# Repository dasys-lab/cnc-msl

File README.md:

# cnc-msl 
[Reference](https://carpe-noctem-cassel.github.io/cnc-msl) | [Documentation](https://carpe-noctem-cassel.github.io)

Domain-specific stuff of Carpe Noctem Cassel Middle Size League stuff...

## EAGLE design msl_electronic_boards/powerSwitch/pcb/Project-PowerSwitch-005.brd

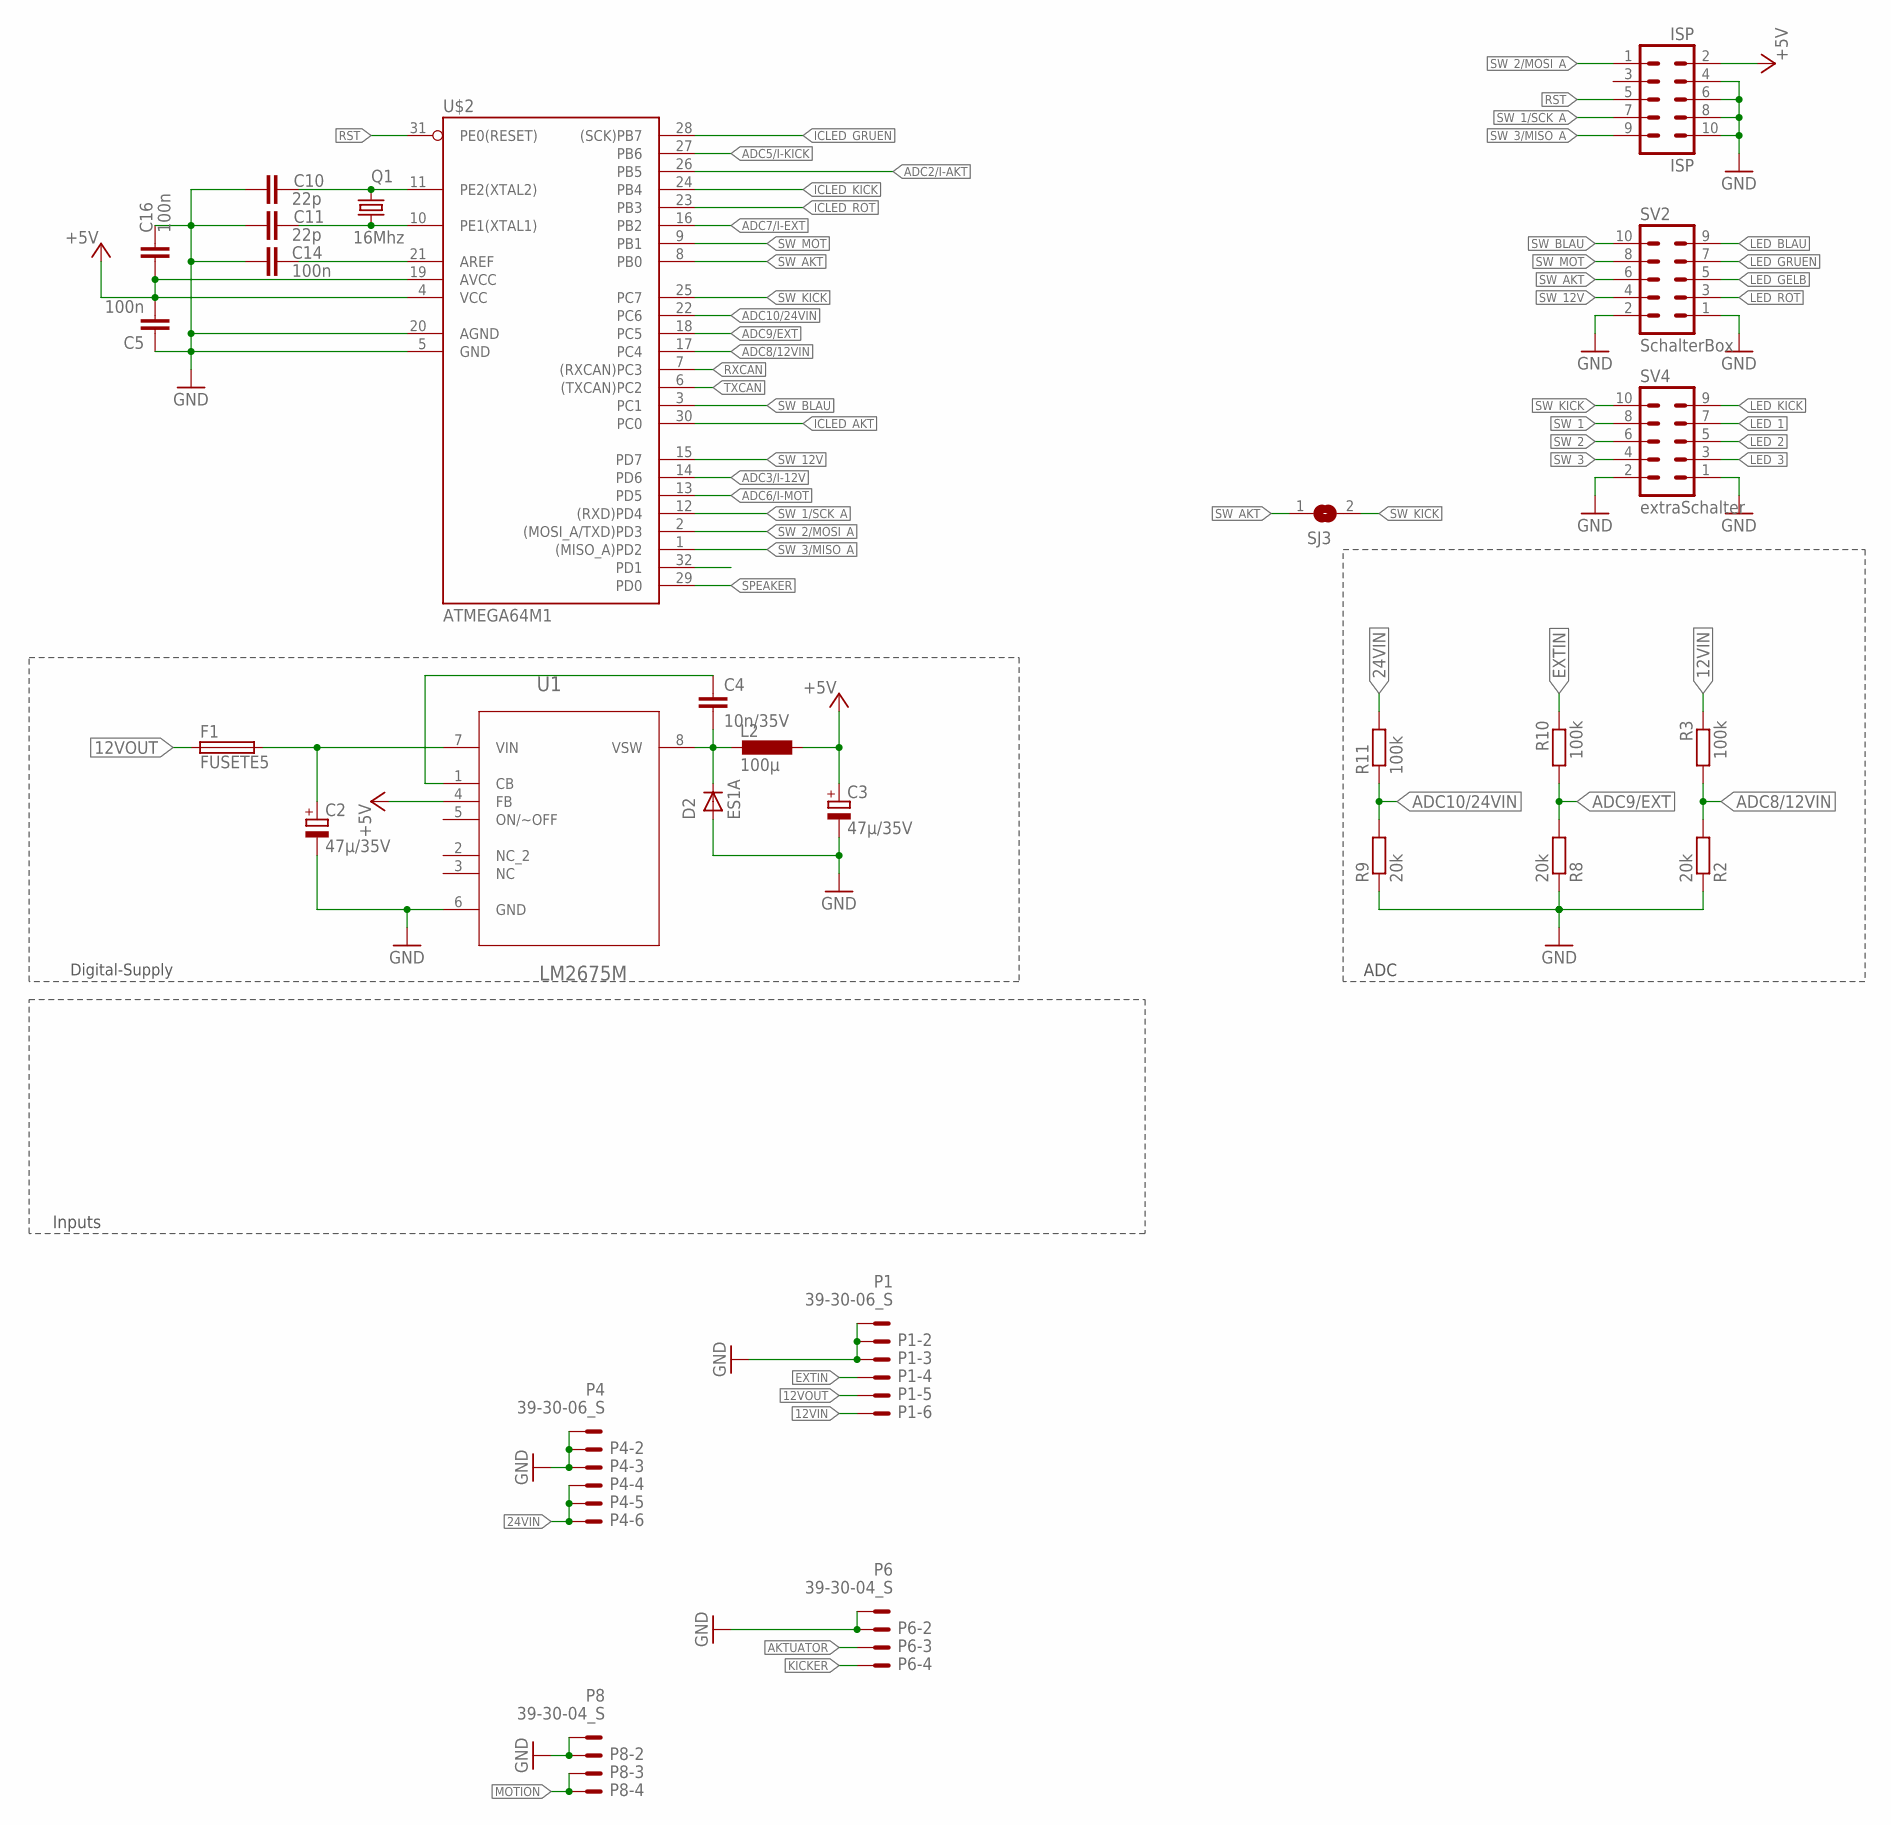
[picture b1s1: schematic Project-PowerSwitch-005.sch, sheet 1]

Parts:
C2, C3: 47µ/35V; PANASONIC_D
C4: 10n/35V; C0603
C5, C14, C16: 100n; C0603
C10, C11: 22p; C0603
D2: ES1A; SMA-DO214AC
F1: FUSETE5; TE5
ISP: ISP; ML10
L2: 100µ; PISM
P1, P4: 39-30-06_S; 39-30-?06?
P6, P8: 39-30-04_S; 39-30-?04?
Q1: 16Mhz; HC49UP
R2, R8, R9: 20k; R0805
R3, R10, R11: 100k; R0805
SJ3: SJ
SV2: SchalterBox; ML10
SV4: extraSchalter; ML10
U1: LM2675M; SOIC127P620X175-8N
U$2: ATMEGA64M1; TQFP32-08

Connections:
12VIN: P1.6, R3.1; also elsewhere on the board
12VOUT: F1.1, P1.5; also elsewhere on the board
24VIN: P4.4, P4.5, P4.6, R11.2; also elsewhere on the board
+5V: C3.+, C5.2, C16.1, ISP.2, L2.1, U1.4 (FB), U$2.4 (VCC), U$2.19 (AVCC); also elsewhere on the board
ADC2/I-AKT: U$2.26 (PB5); also elsewhere on the board
ADC3/I-12V: U$2.14 (PD6); also elsewhere on the board
ADC5/I-KICK: U$2.27 (PB6); also elsewhere on the board
ADC6/I-MOT: U$2.13 (PD5); also elsewhere on the board
ADC7/I-EXT: U$2.16 (PB2); also elsewhere on the board
ADC8/12VIN: R2.2, R3.2, U$2.17 (PC4)
ADC9/EXT: R8.2, R10.2, U$2.18 (PC5)
ADC10/24VIN: R9.2, R11.1, U$2.22 (PC6)
AKTUATOR: P6.3; also elsewhere on the board
EXTIN: P1.4, R10.1; also elsewhere on the board
GND: C2.-, C3.-, C5.1, C10.1, C11.1, C14.1, C16.2, D2.A, ISP.4, ISP.6, ISP.8, ISP.10, P1.1, P1.2, P1.3, P4.1, P4.2, P4.3, P6.1, P6.2, P8.1, P8.2, R2.1, R8.1, R9.1, SV2.1, SV2.2, SV4.1, SV4.2, U1.6 (GND), U$2.5 (GND), U$2.20 (AGND); also elsewhere on the board
ICLED_AKT: U$2.30 (PC0); also elsewhere on the board
ICLED_GRUEN: U$2.28 ((SCK)PB7); also elsewhere on the board
ICLED_KICK: U$2.24 (PB4); also elsewhere on the board
ICLED_ROT: U$2.23 (PB3); also elsewhere on the board
KICKER: P6.4; also elsewhere on the board
LED_1: SV4.7
LED_2: SV4.5
LED_3: SV4.3
LED_BLAU: SV2.9; also elsewhere on the board
LED_GELB: SV2.5; also elsewhere on the board
LED_GRUEN: SV2.7; also elsewhere on the board
LED_KICK: SV4.9; also elsewhere on the board
LED_ROT: SV2.3; also elsewhere on the board
MOTION: P8.3, P8.4; also elsewhere on the board
unnamed: C10.2, Q1.2, U$2.11 (PE2(XTAL2))
unnamed: C11.2, Q1.1, U$2.10 (PE1(XTAL1))
unnamed: C14.2, U$2.21 (AREF)
unnamed: C2.+, F1.2, U1.7 (VIN)
unnamed: C4.2, D2.K (C), L2.2, U1.8 (VSW)
unnamed: C4.1, U1.1 (CB)
RST: ISP.5, U$2.31 (PE0(RESET))
RXCAN: U$2.7 ((RXCAN)PC3); also elsewhere on the board
SPEAKER: U$2.29 (PD0); also elsewhere on the board
SW_1: SV4.8
SW_1/SCK_A: ISP.7, U$2.12 ((RXD)PD4)
SW_2: SV4.6
SW_2/MOSI_A: ISP.1, U$2.2 ((MOSI_A/TXD)PD3)
SW_3: SV4.4
SW_3/MISO_A: ISP.9, U$2.1 ((MISO_A)PD2)
SW_12V: SV2.4, U$2.15 (PD7); also elsewhere on the board
SW_AKT: SJ3.1, SV2.6, U$2.8 (PB0); also elsewhere on the board
SW_BLAU: SV2.10, U$2.3 (PC1)
SW_KICK: SJ3.2, SV4.10, U$2.25 (PC7); also elsewhere on the board
SW_MOT: SV2.8, U$2.9 (PB1); also elsewhere on the board
TXCAN: U$2.6 ((TXCAN)PC2); also elsewhere on the board

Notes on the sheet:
Inputs
ADC
Digital-Supply

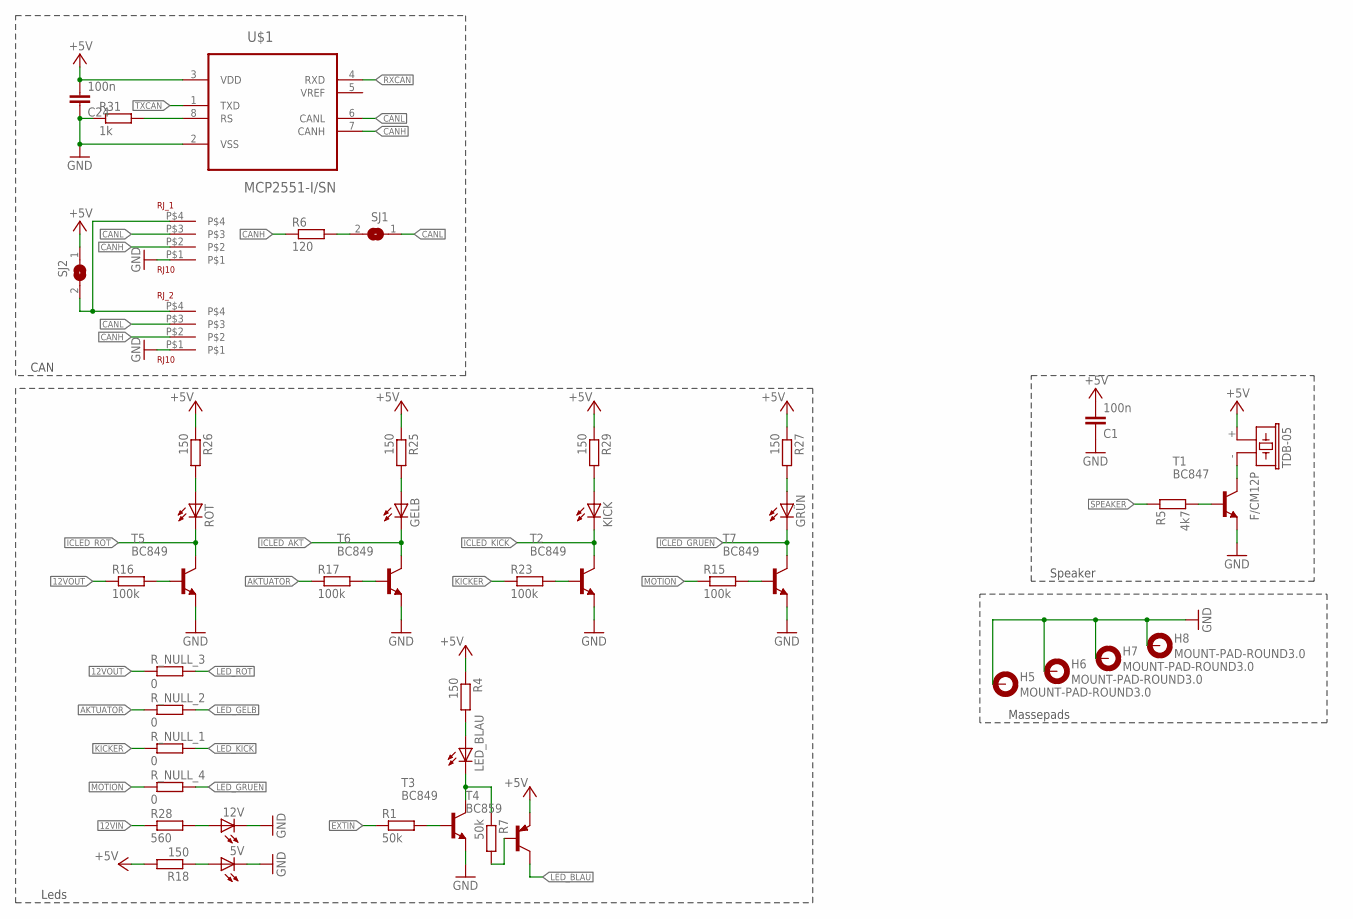
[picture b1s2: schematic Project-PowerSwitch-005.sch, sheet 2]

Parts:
5V, 12V: LEDCHIPLED_0805; CHIPLED_0805
C1, C24: 100n; C0603
GELB: LEDCHIPLED_0805; CHIPLED_0805
GRÜN: LEDCHIPLED_0805; CHIPLED_0805
H5, H6, H7, H8: MOUNT-PAD-ROUND3.0; 3,0-PAD
KICK: LEDCHIPLED_0805; CHIPLED_0805
LED_BLAU: LEDCHIPLED_0805; CHIPLED_0805
R1, R7: 50k; R0805
R4, R18, R25, R26, R27, R29: 150; R0805
R5: 4k7; R0805
R6: 120; M0805
R15, R16, R17, R23: 100k; R0805
R28: 560; R0805
R31: 1k; R0805
RJ_1, RJ_2: RJ10
ROT: LEDCHIPLED_0805; CHIPLED_0805
R_NULL_1, R_NULL_2, R_NULL_3, R_NULL_4: 0; R0402
SJ1, SJ2: SJ
T1: BC847; SOT23
T2, T3, T5, T6, T7: BC849; SOT23
T4: BC859; SOT23-BEC
TDB-05: F/CM12P
U$1: MCP2551-I/SN; SOIC127P600X175-8N

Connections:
12VIN: R28.1; also elsewhere on the board
12VOUT: R16.1, R_NULL_3.1; also elsewhere on the board
+5V: C1.2, C24.2, R4.1, R18.2, R25.1, R26.1, R27.1, R29.1, SJ2.1, T4.E, TDB-05.+ (1), U$1.3 (VDD); also elsewhere on the board
AKTUATOR: R17.1, R_NULL_2.1; also elsewhere on the board
CANH: R6.1, RJ_1.P$2, RJ_2.P$2, U$1.7 (CANH)
CANL: RJ_1.P$3, RJ_2.P$3, SJ1.1, U$1.6 (CANL)
EXTIN: R1.1; also elsewhere on the board
GND: 5V.C, 12V.C, C1.1, C24.1, H5.B3,0, H6.B3,0, H7.B3,0, H8.B3,0, R31.1, RJ_1.P$1, RJ_2.P$1, T1.2 (E), T2.2 (E), T3.2 (E), T5.2 (E), T6.2 (E), T7.2 (E), U$1.2 (VSS); also elsewhere on the board
ICLED_AKT: GELB.C, T6.3 (C); also elsewhere on the board
ICLED_GRUEN: GRÜN.C, T7.3 (C); also elsewhere on the board
ICLED_KICK: KICK.C, T2.3 (C); also elsewhere on the board
ICLED_ROT: ROT.C, T5.3 (C); also elsewhere on the board
KICKER: R23.1, R_NULL_1.1; also elsewhere on the board
LED_BLAU: T4.C; also elsewhere on the board
LED_GELB: R_NULL_2.2; also elsewhere on the board
LED_GRUEN: R_NULL_4.2; also elsewhere on the board
LED_KICK: R_NULL_1.2; also elsewhere on the board
LED_ROT: R_NULL_3.2; also elsewhere on the board
MOTION: R15.1, R_NULL_4.1; also elsewhere on the board
unnamed: R5.2, T1.1 (B)
unnamed: RJ_1.P$4, RJ_2.P$4, SJ2.2
unnamed: R23.2, T2.1 (B)
unnamed: KICK.A, R29.2
unnamed: R31.2, U$1.8 (RS)
unnamed: R6.2, SJ1.2
unnamed: GELB.A, R25.2
unnamed: R26.2, ROT.A
unnamed: R1.2, T3.1 (B)
unnamed: LED_BLAU.A, R4.2
unnamed: LED_BLAU.C, R7.1, T3.3 (C)
unnamed: R7.2, T4.B
unnamed: T1.3 (C), TDB-05.- (2)
unnamed: GRÜN.A, R27.2
unnamed: 12V.A, R28.2
unnamed: R16.2, T5.1 (B)
unnamed: R17.2, T6.1 (B)
unnamed: R15.2, T7.1 (B)
unnamed: 5V.A, R18.1
RXCAN: U$1.4 (RXD); also elsewhere on the board
SPEAKER: R5.1; also elsewhere on the board
TXCAN: U$1.1 (TXD); also elsewhere on the board

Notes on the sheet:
CAN
Speaker
Massepads
Leds

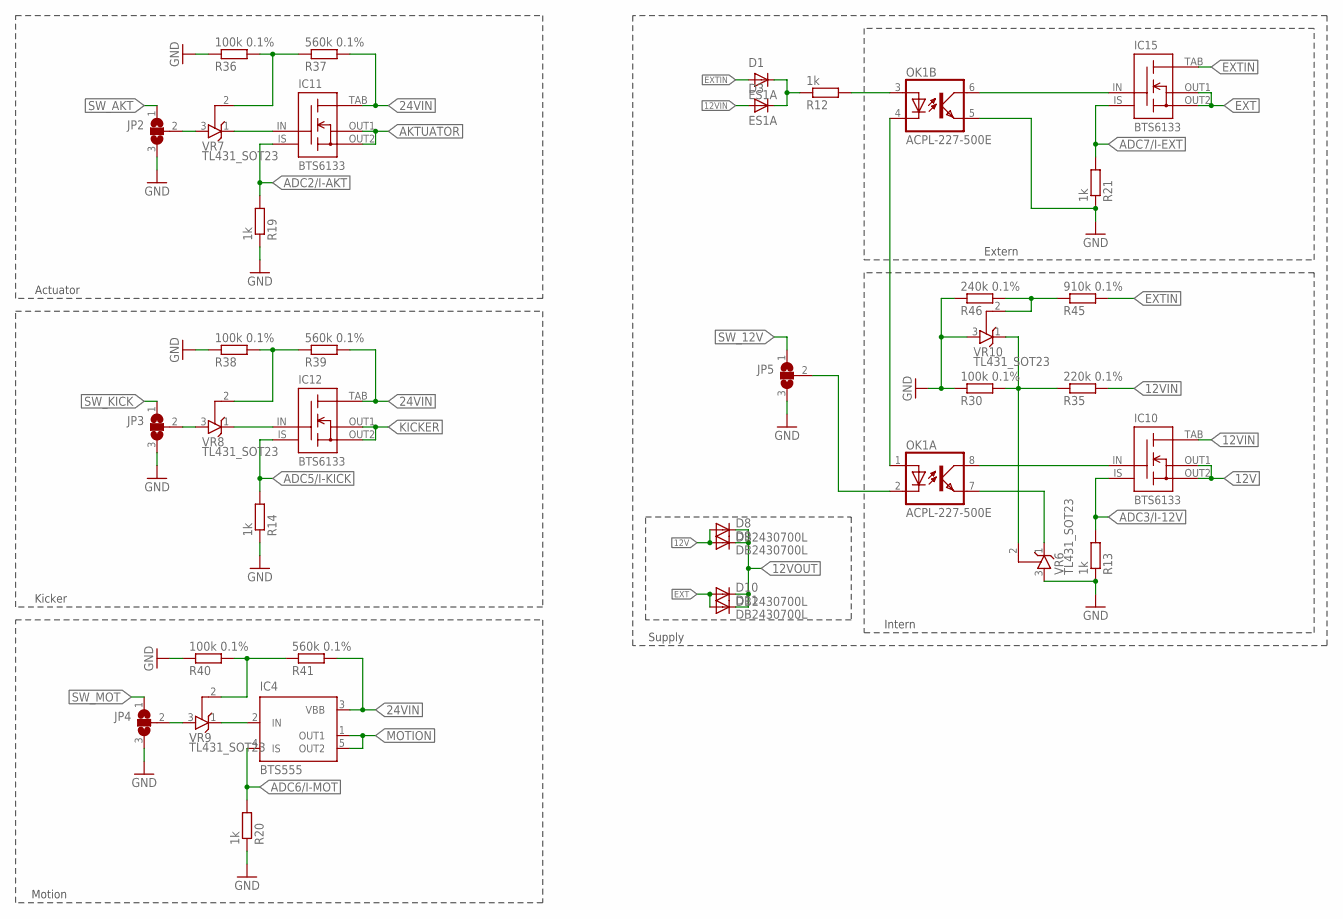
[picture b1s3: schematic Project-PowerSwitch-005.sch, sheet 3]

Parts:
D1, D3: ES1A; SMA-DO214AC
D8, D9, D10, D11: DB2430700L; TMINIP2-F2-B
IC4: BTS555; TO220-51
IC10, IC11, IC12, IC15: BTS6133; TO252-51
JP2, JP3, JP4, JP5: SJ2W; SJ_2
OK1: ACPL-227-500E; SOIC08
R12, R13, R14, R19, R20, R21: 1k; R0805
R30, R36, R38, R40: 100k 0.1%; R0805
R35: 220k 0.1%; R0805
R37, R39, R41: 560k 0.1%; R0805
R45: 910k 0.1%; R0805
R46: 240k 0.1%; R0805
VR6, VR7, VR8, VR9, VR10: TL431_SOT23; SOT23

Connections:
12V: D8.A, D9.A, IC10.OUT1 (OUT), IC10.OUT2 (OUT)
12VIN: D3.A, IC10.TAB (VBB), R35.2; also elsewhere on the board
12VOUT: D8.C, D9.C, D10.C, D11.C; also elsewhere on the board
24VIN: IC4.3 (VBB), IC11.TAB (VBB), IC12.TAB (VBB), R37.2, R39.2, R41.2; also elsewhere on the board
ADC2/I-AKT: IC11.IS, R19.2; also elsewhere on the board
ADC3/I-12V: IC10.IS, R13.2; also elsewhere on the board
ADC5/I-KICK: IC12.IS, R14.2; also elsewhere on the board
ADC6/I-MOT: IC4.4 (IS), R20.2; also elsewhere on the board
ADC7/I-EXT: IC15.IS, R21.2; also elsewhere on the board
AKTUATOR: IC11.OUT1 (OUT), IC11.OUT2 (OUT); also elsewhere on the board
EXT: D10.A, D11.A, IC15.OUT1 (OUT), IC15.OUT2 (OUT)
EXTIN: D1.A, IC15.TAB (VBB), R45.2; also elsewhere on the board
GND: JP2.3, JP3.3, JP4.3, JP5.3, OK1.5 (EMIT), R13.1, R14.1, R19.1, R20.1, R21.1, R30.1, R36.1, R38.1, R40.1, R46.1, VR6.3 (A), VR10.3 (A); also elsewhere on the board
KICKER: IC12.OUT1 (OUT), IC12.OUT2 (OUT); also elsewhere on the board
MOTION: IC4.1 (OUT1), IC4.5 (OUT2); also elsewhere on the board
unnamed: JP2.2, VR7.3 (A)
unnamed: JP5.2, OK1.2 (C)
unnamed: JP3.2, VR8.3 (A)
unnamed: JP4.2, VR9.3 (A)
unnamed: D1.K (C), D3.K (C), R12.1
unnamed: OK1.1 (A), OK1.4 (C)
unnamed: OK1.3 (A), R12.2
unnamed: OK1.7 (EMIT), VR6.1 (C)
unnamed: IC15.IN, OK1.6 (COL)
unnamed: IC10.IN, OK1.8 (COL)
unnamed: R30.2, R35.1, VR6.2 (R), VR10.1 (C)
unnamed: IC12.IN, VR8.1 (C)
unnamed: IC4.2 (IN), VR9.1 (C)
unnamed: IC11.IN, VR7.1 (C)
unnamed: R36.2, R37.1, VR7.2 (R)
unnamed: R38.2, R39.1, VR8.2 (R)
unnamed: R40.2, R41.1, VR9.2 (R)
unnamed: R45.1, R46.2, VR10.2 (R)
SW_12V: JP5.1; also elsewhere on the board
SW_AKT: JP2.1; also elsewhere on the board
SW_KICK: JP3.1; also elsewhere on the board
SW_MOT: JP4.1; also elsewhere on the board

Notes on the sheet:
Intern
Extern
Supply
Motion
Kicker
Actuator

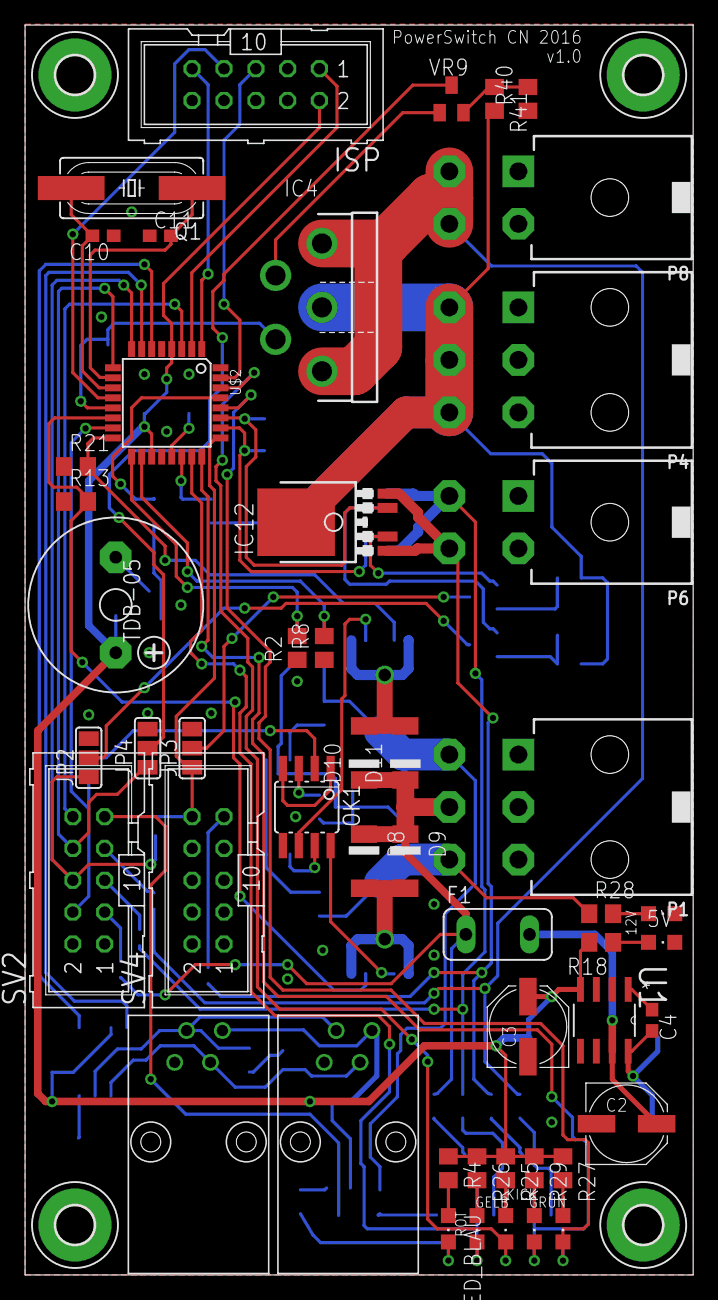
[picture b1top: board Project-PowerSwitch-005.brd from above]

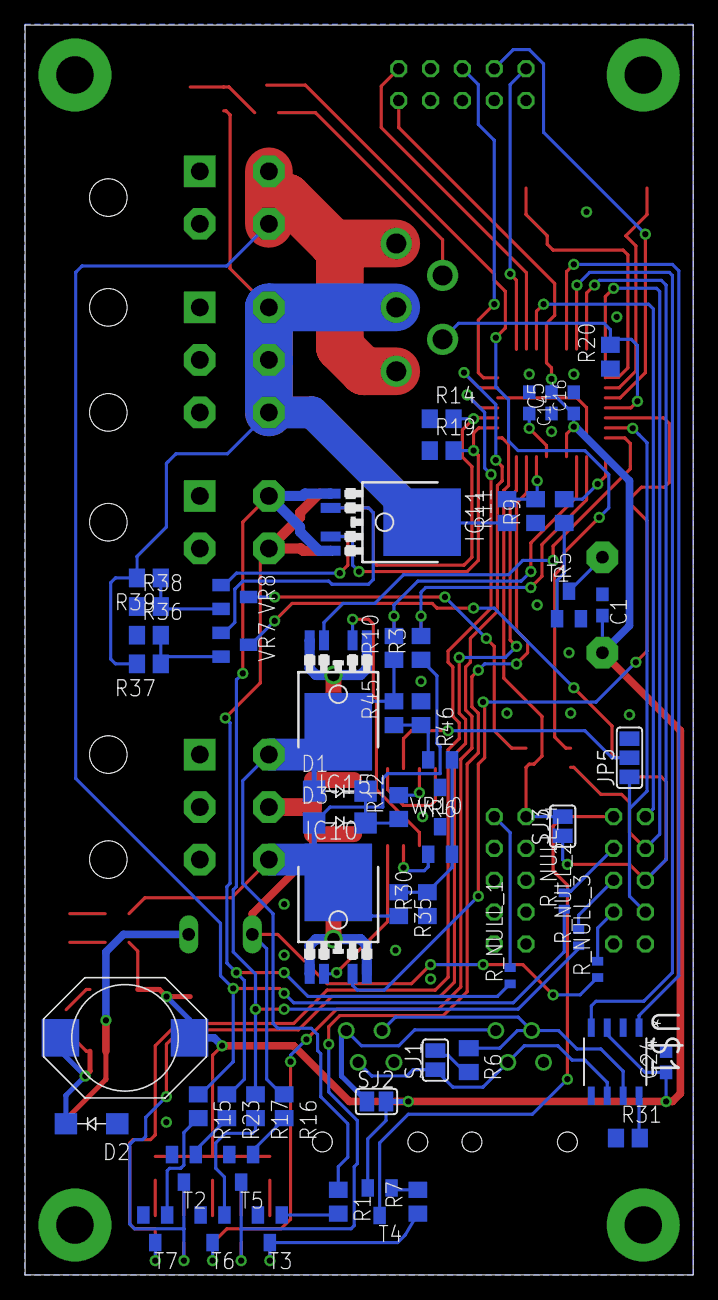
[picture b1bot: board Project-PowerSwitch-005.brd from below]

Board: 4 copper layers, 53.3 x 99.7 mm, 111 parts (57 on the bottom side), 85 nets.

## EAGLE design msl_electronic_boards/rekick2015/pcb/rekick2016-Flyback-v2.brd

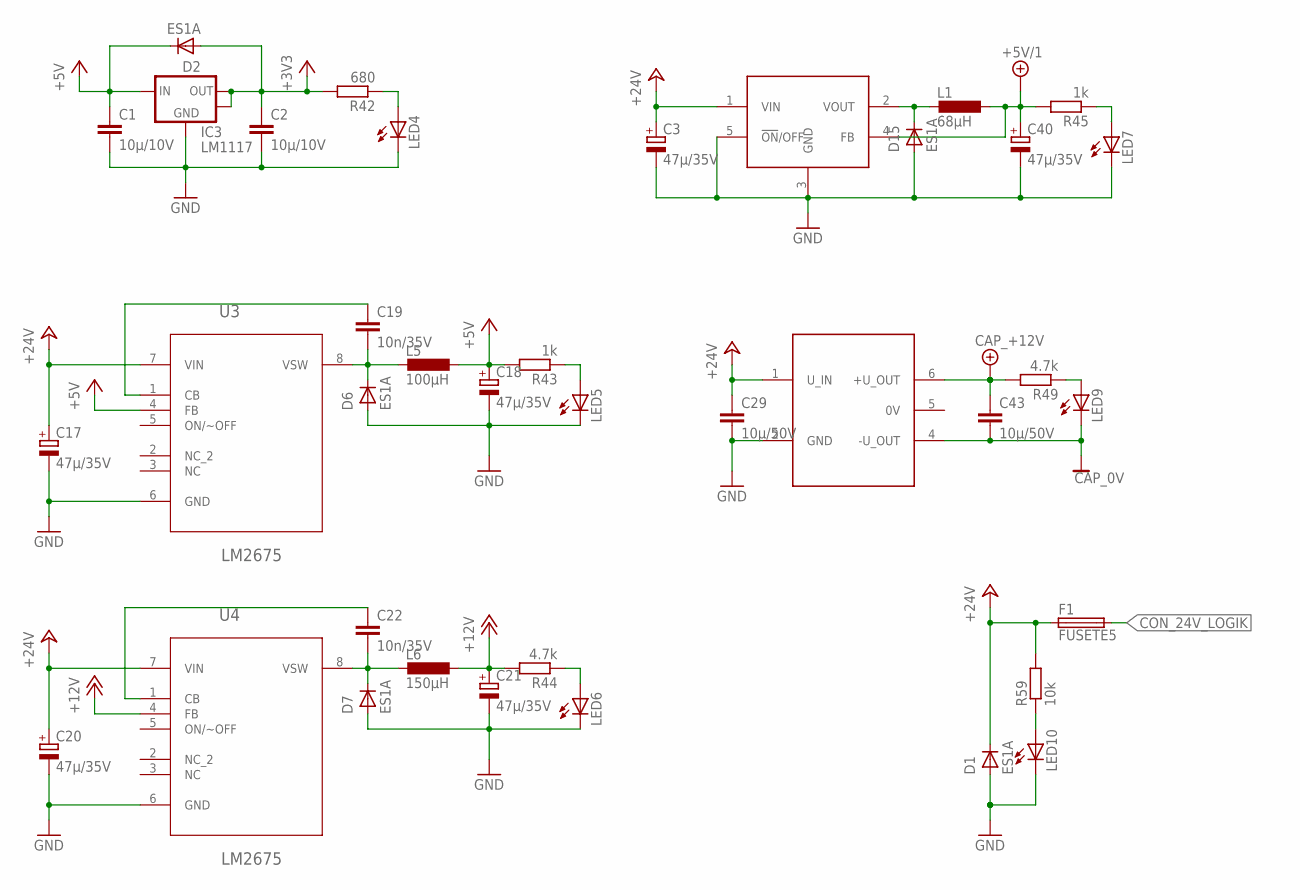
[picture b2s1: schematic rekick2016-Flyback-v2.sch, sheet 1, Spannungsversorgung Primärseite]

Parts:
C1, C2: 10µ/10V; C0603
C3, C17, C18, C20, C21, C40: 47µ/35V; PANASONIC_D
C19, C22: 10n/35V; C0603
C29, C43: 10µ/50V; C1206
D1, D2, D6, D7, D15: ES1A; SMA-DO214AC
F1: FUSETE5; TE5
IC3: LM1117; SOT223
L1: 68µH; PISM
L5: 100µH; PISM
L6: 150µH; PISM
LED4, LED5, LED6, LED7, LED9, LED10: LEDCHIP-LED0805; CHIP-LED0805
R42: 680; R0805
R43, R45: 1k; R0805
R44, R49: 4.7k; R0805
R59: 10k; R0805
U3, U4: LM2675; SOIC127P620X175-8N
U$4: TMH-D
U$8: LM2576; TO220511

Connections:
+3V3: C2.1, D2.A, IC3.2 (OUT), IC3.4 (OUT), R42.2; also elsewhere on the board
+5V: C1.1, C18.+, D2.K (C), IC3.3 (IN), L5.1, R43.2, U3.4 (FB); also elsewhere on the board
+5V/1: C40.+, L1.1, R45.2, U$8.4 (FB); also elsewhere on the board
+12V: C21.+, L6.1, R44.2, U4.4 (FB); also elsewhere on the board
+24V: C3.+, C17.+, C20.+, C29.1, D1.K (C), F1.1, R59.2, U3.7 (VIN), U4.7 (VIN), U$4.1 (U_IN), U$8.1 (VIN); also elsewhere on the board
CAP_0V: C43.2, LED9.C, U$4.4 (-U_OUT); also elsewhere on the board
CAP_+12V: C43.1, R49.2, U$4.6 (+U_OUT); also elsewhere on the board
CON_24V_LOGIK: F1.2; also elsewhere on the board
GND: C1.2, C2.2, C3.-, C17.-, C18.-, C20.-, C21.-, C29.2, C40.-, D1.A, D6.A, D7.A, D15.A, IC3.1 (GND), LED4.C, LED5.C, LED6.C, LED7.C, LED10.C, U3.6 (GND), U4.6 (GND), U$4.2 (GND), U$8.3 (GND), U$8.5 (!ON!/OFF); also elsewhere on the board
unnamed: C19.2, D6.K (C), L5.2, U3.8 (VSW)
unnamed: C19.1, U3.1 (CB)
unnamed: C22.2, D7.K (C), L6.2, U4.8 (VSW)
unnamed: C22.1, U4.1 (CB)
unnamed: LED4.A, R42.1
unnamed: D15.K (C), L1.2, U$8.2 (VOUT)
unnamed: LED7.A, R45.1
unnamed: LED5.A, R43.1
unnamed: LED6.A, R44.1
unnamed: LED9.A, R49.1
unnamed: LED10.A, R59.1

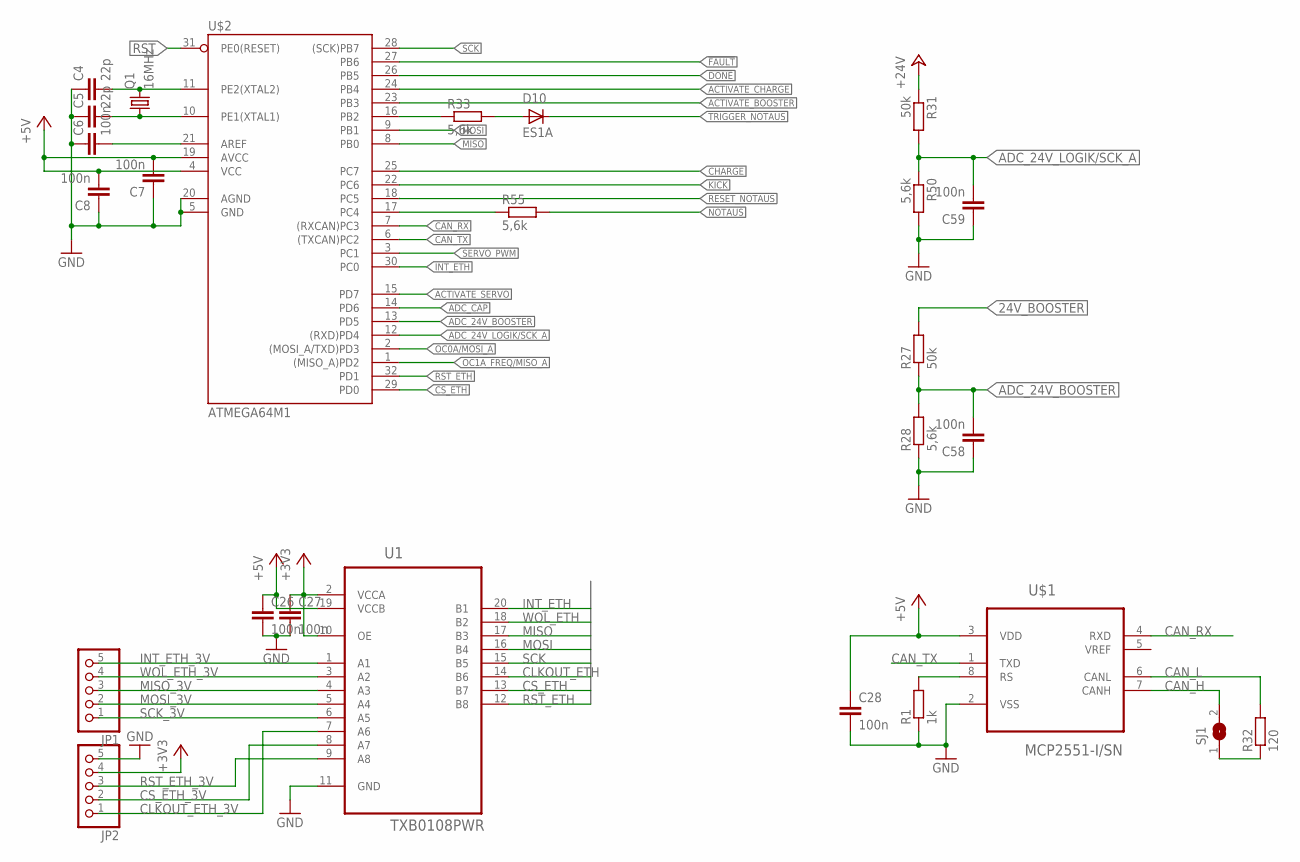
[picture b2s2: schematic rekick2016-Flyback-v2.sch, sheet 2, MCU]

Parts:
C4, C5: 22p; C0603
C6, C7, C8, C26, C27, C28, C58, C59: 100n; C0603
D10: ES1A; SMA-DO214AC
JP1, JP2: PINHD-1X5; 1X05
Q1: 16MHz; HC49UP
R1: 1k; R0805
R27, R31: 50k; R0805
R28, R33, R50, R55: 5,6k; R0805
R32: 120; R0805
SJ1: SJ
U1: TXB0108PWR; SOP65P640X120-20N
U$1: MCP2551-I/SN; SOIC127P600X175-8N
U$2: ATMEGA64M1; TQFP32-08

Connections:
24V_BOOSTER: R27.2; also elsewhere on the board
!DONE: U$2.26 (PB5); also elsewhere on the board
!FAULT: U$2.27 (PB6); also elsewhere on the board
+3V3: C27.1, JP2.4, U1.2 (VCCA), U1.10 (OE); also elsewhere on the board
+5V: C7.2, C8.2, C26.1, C28.1, U1.19 (VCCB), U$1.3 (VDD), U$2.4 (VCC), U$2.19 (AVCC); also elsewhere on the board
+24V: R31.1; also elsewhere on the board
ACTIVATE_BOOSTER: U$2.23 (PB3); also elsewhere on the board
ACTIVATE_CHARGE: U$2.24 (PB4); also elsewhere on the board
ACTIVATE_SERVO: U$2.15 (PD7); also elsewhere on the board
ADC_24V_BOOSTER: C58.2, R27.1, R28.2, U$2.13 (PD5)
ADC_24V_LOGIK/SCK_A: C59.2, R31.2, R50.1, U$2.12 ((RXD)PD4); also elsewhere on the board
ADC_CAP: U$2.14 (PD6); also elsewhere on the board
CAN_H: SJ1.2, U$1.7 (CANH); also elsewhere on the board
CAN_L: R32.2, U$1.6 (CANL); also elsewhere on the board
CAN_RX: U$1.4 (RXD), U$2.7 ((RXCAN)PC3)
CAN_TX: U$1.1 (TXD), U$2.6 ((TXCAN)PC2)
CHARGE: U$2.25 (PC7); also elsewhere on the board
CLKOUT_ETH: U1.14 (B6)
CLKOUT_ETH_3V: JP2.1, U1.7 (A6)
CS_ETH: U1.13 (B7), U$2.29 (PD0)
CS_ETH_3V: JP2.2, U1.8 (A7)
GND: C4.1, C5.1, C6.1, C7.1, C8.1, C26.2, C27.2, C28.2, C58.1, C59.1, JP2.5, R1.1, R28.1, R50.2, U1.11 (GND), U$1.2 (VSS), U$2.5 (GND), U$2.20 (AGND); also elsewhere on the board
INT_ETH: U1.20 (B1), U$2.30 (PC0)
INT_ETH_3V: JP1.5, U1.1 (A1)
IN_NOTAUS: R55.1, U$2.17 (PC4)
KICK: U$2.22 (PC6); also elsewhere on the board
MISO: U1.17 (B3), U$2.8 (PB0)
MISO_3V: JP1.3, U1.4 (A3)
MOSI: U1.16 (B4), U$2.9 (PB1)
MOSI_3V: JP1.2, U1.5 (A4)
unnamed: R1.2, U$1.8 (RS)
unnamed: C4.2, Q1.2, U$2.11 (PE2(XTAL2))
unnamed: C5.2, Q1.1, U$2.10 (PE1(XTAL1))
unnamed: R32.1, SJ1.1
unnamed: C6.2, U$2.21 (AREF)
unnamed: D10.A, R33.2
NOTAUS: R55.2; also elsewhere on the board
OC0A/MOSI_A: U$2.2 ((MOSI_A/TXD)PD3); also elsewhere on the board
OC1A_FREQ/MISO_A: U$2.1 ((MISO_A)PD2); also elsewhere on the board
OUT_TRIGGER_NOTAUS: R33.1, U$2.16 (PB2)
RESET_NOTAUS: U$2.18 (PC5); also elsewhere on the board
RST: U$2.31 (PE0(RESET)); also elsewhere on the board
RST_ETH: U1.12 (B8), U$2.32 (PD1)
RST_ETH_3V: JP2.3, U1.9 (A8)
SCK: U1.15 (B5), U$2.28 ((SCK)PB7)
SCK_3V: JP1.1, U1.6 (A5)
SERVO_PWM: U$2.3 (PC1); also elsewhere on the board
TRIGGER_NOTAUS: D10.K (C); also elsewhere on the board
WOL_ETH: U1.18 (B2)
WOL_ETH_3V: JP1.4, U1.3 (A2)

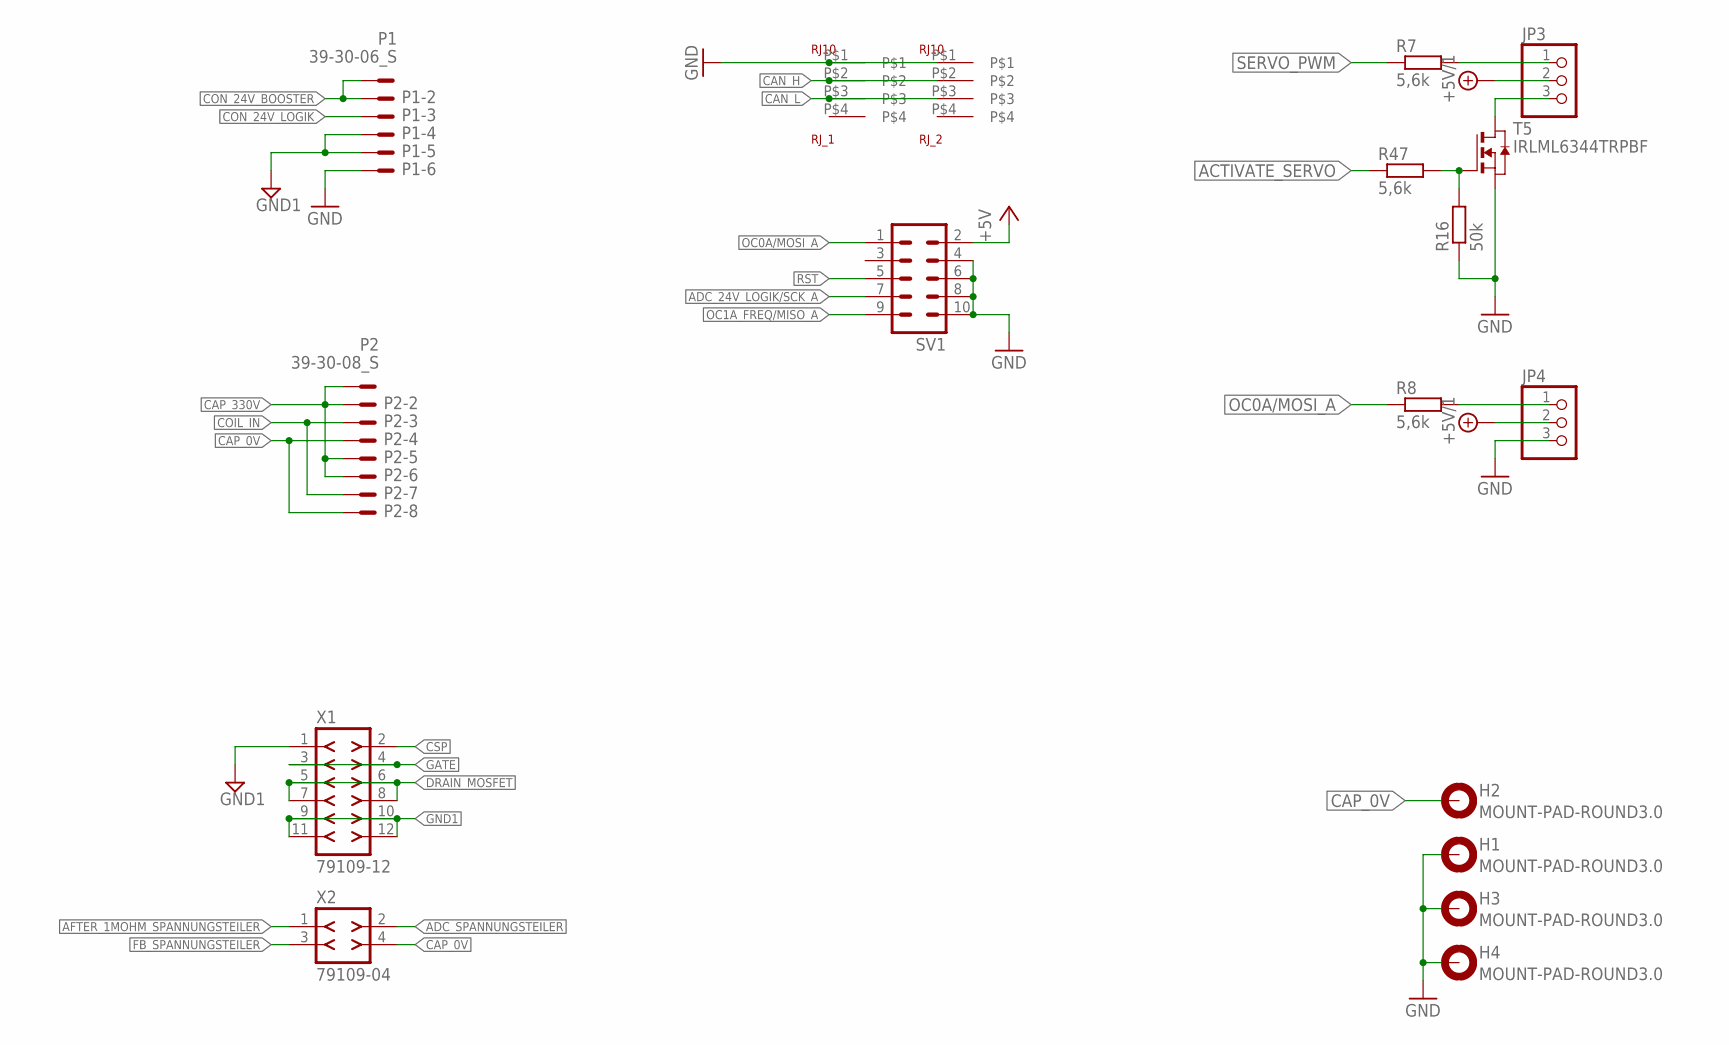
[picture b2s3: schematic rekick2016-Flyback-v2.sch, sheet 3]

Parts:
H1, H2, H3, H4: MOUNT-PAD-ROUND3.0; 3,0-PAD
JP3: PINHD-1X3/90; 1X03/90
JP4: PINHD-1X3; 1X03
P1: 39-30-06_S; 39-30-?06?
P2: 39-30-08_S; 39-30-?08?
R7, R8, R47: 5,6k; R0805
R16: 50k; R0805
RJ_1, RJ_2: RJ10
SV1: ML10
T5: IRLML6344TRPBF; SOT-23
X1: 79109-12
X2: 79109-04

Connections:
+5V: SV1.2; also elsewhere on the board
+5V/1: JP3.2, JP4.2; also elsewhere on the board
ACTIVATE_SERVO: R47.1; also elsewhere on the board
ADC_24V_LOGIK/SCK_A: SV1.7; also elsewhere on the board
ADC_SPANNUNGSTEILER: X2.2; also elsewhere on the board
AFTER_1MOHM_SPANNUNGSTEILER: X2.1; also elsewhere on the board
CAN_H: RJ_1.P$2, RJ_2.P$2; also elsewhere on the board
CAN_L: RJ_1.P$3, RJ_2.P$3; also elsewhere on the board
CAP_0V: H2.B3,0, P2.4, P2.8, X2.4; also elsewhere on the board
CAP_330V: P2.1, P2.2, P2.5, P2.6; also elsewhere on the board
COIL_IN: P2.3, P2.7; also elsewhere on the board
CON_24V_BOOSTER: P1.1, P1.2; also elsewhere on the board
CON_24V_LOGIK: P1.3; also elsewhere on the board
CSP: X1.2; also elsewhere on the board
DRAIN_MOSFET: X1.5, X1.6, X1.7, X1.8; also elsewhere on the board
FB_SPANNUNGSTEILER: X2.3; also elsewhere on the board
GATE: X1.3, X1.4; also elsewhere on the board
GND: H1.B3,0, H3.B3,0, H4.B3,0, JP4.3, P1.6, R16.1, RJ_1.P$1, RJ_2.P$1, SV1.4, SV1.6, SV1.8, SV1.10, T5.2 (S); also elsewhere on the board
GND1: P1.4, P1.5, X1.1, X1.9, X1.10, X1.11, X1.12; also elsewhere on the board
unnamed: JP3.1, R7.2
unnamed: JP4.1, R8.2
unnamed: JP3.3, T5.1 (D)
unnamed: R16.2, R47.2, T5.3 (G)
OC0A/MOSI_A: R8.1, SV1.1; also elsewhere on the board
OC1A_FREQ/MISO_A: SV1.9; also elsewhere on the board
RST: SV1.5; also elsewhere on the board
SERVO_PWM: R7.1; also elsewhere on the board

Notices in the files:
parts and their libraries:
con-molex-mini-fit: Copyright (C) 2011, Bob Starr
EagleLibrary_Wuerth_Elektronik_eiSos_rev: Copyright: Würth Elektronik
con-molex-milli-grid: Copyright (C) 2010, Bob Starr
